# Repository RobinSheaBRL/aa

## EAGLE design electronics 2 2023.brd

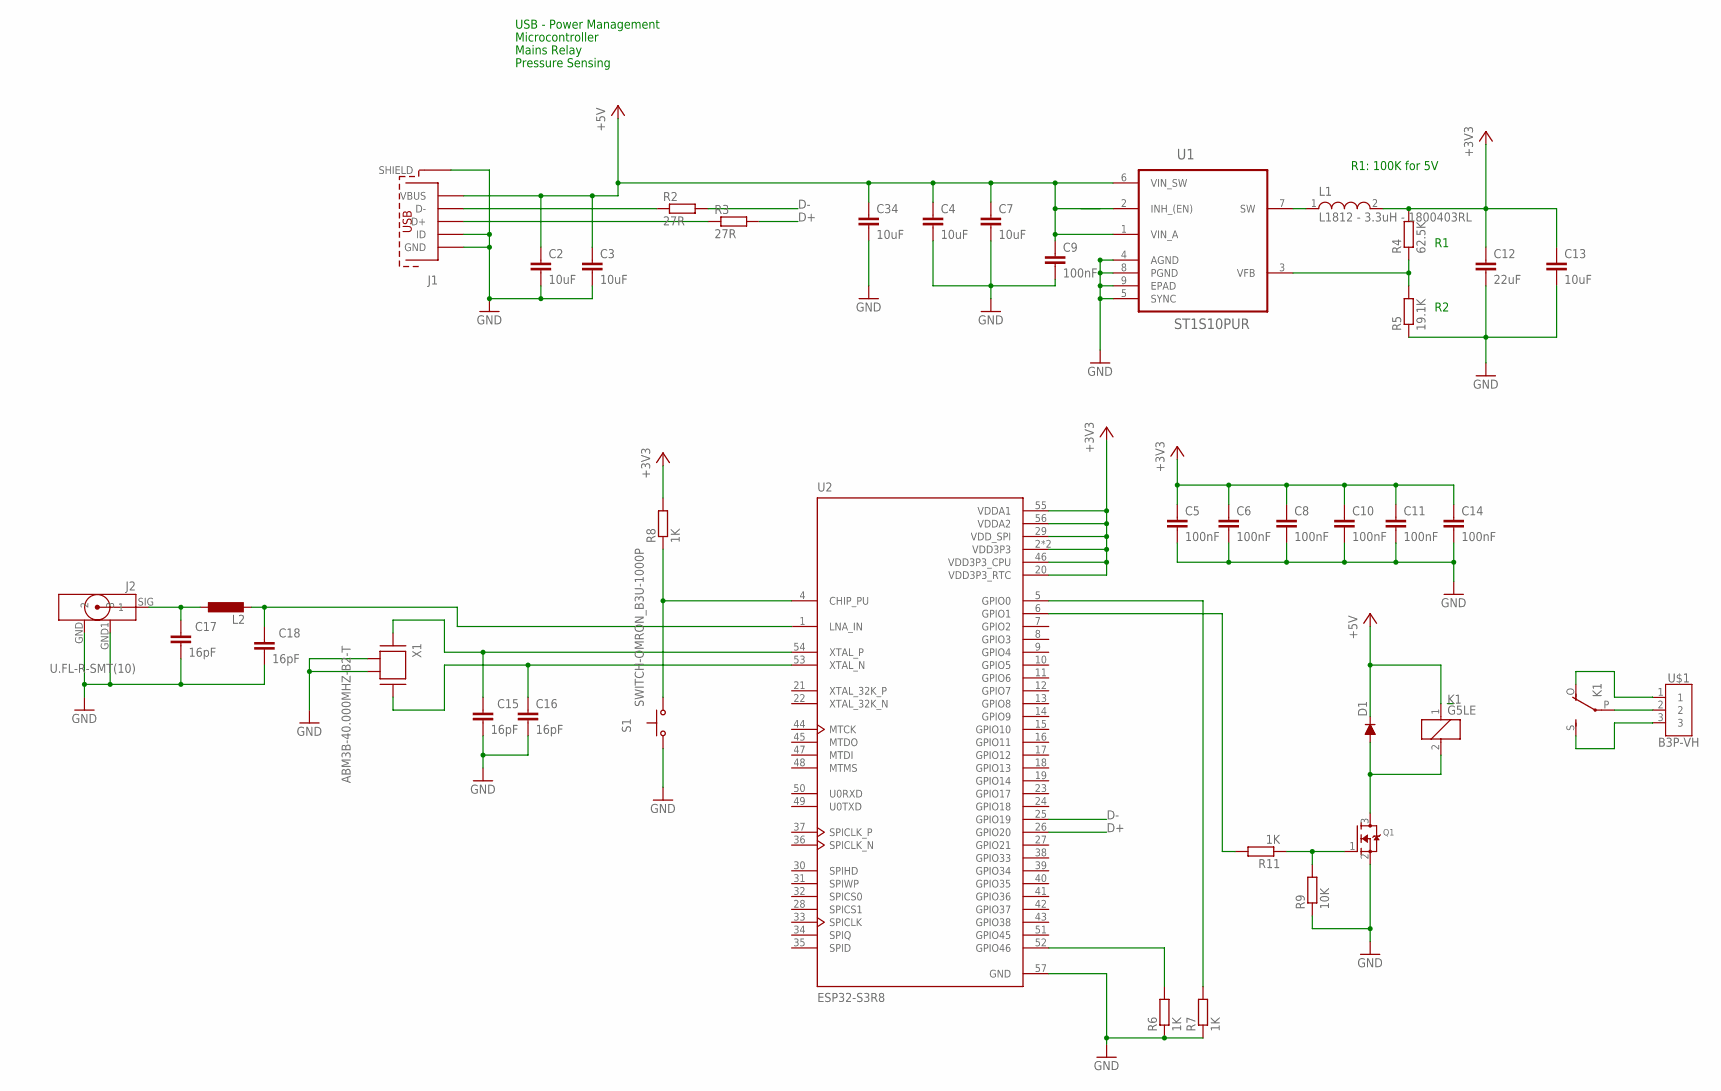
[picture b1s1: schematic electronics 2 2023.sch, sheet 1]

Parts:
C2, C3, C4, C7, C13, C34: 10uF; C0603
C5, C6, C8, C9, C10, C11, C14: 100nF; C0402
C12: 22uF; C0603
C15, C16, C17, C18: 16pF; C0402
D1: DIODE_DIODE-SOD123; DIODE_SOD123
J1: MICRO-USB-SOCKET; 629105136821
J2: U.FL-R-SMT(10)
K1: G5LE
L1: L1812 - 3.3uH - 1800403RL; L1812
L2: L-EUL2012C; L2012C
Q1: MOSFET-NREFLOW; SOT23
R2, R3: 27R; R0402
R4: 62.5K; R0402
R5: 19.1K; R0402
R6, R7, R8, R11: 1K; R0402
R9: 10K; R0402
S1: SWITCH-OMRON_B3U-1000P
U1: ST1S10PUR; DFN400X400X100-9N
U2: ESP32-S3R8; QFN40P700X700X90-57N
U$1: B3P-VH; B3P-VH_396_3N
X1: ABM3B-40.000MHZ-B2-T

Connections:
+3V3: C5.1, C6.1, C8.1, C10.1, C11.1, C12.1, C13.1, C14.1, L1.2, R4.2, R8.2, U2.2 (VDD3P3), U2.3 (VDD3P3), U2.20 (VDD3P3_RTC), U2.29 (VDD_SPI), U2.46 (VDD3P3_CPU), U2.55 (VDDA1), U2.56 (VDDA2); also elsewhere on the board
+5V: C2.1, C3.1, C4.1, C7.1, C9.1, C34.1, D1.C, J1.1 (VBUS), K1.1, U1.1 (VIN_A), U1.2 (INH_(EN)), U1.6 (VIN_SW)
D+: R3.2, U2.26 (GPIO20)
D-: R2.2, U2.25 (GPIO19)
GND: C2.2, C3.2, C4.2, C5.2, C6.2, C7.2, C8.2, C9.2, C10.2, C11.2, C12.2, C13.2, C14.2, C15.2, C16.2, C17.2, C18.2, C34.2, J1.4 (ID), J1.5 (GND), J1.SHELL (SHIELD), J1.SHELL1 (SHIELD), J1.SHELL2 (SHIELD), J1.SHELL3 (SHIELD), J2.GND (2), J2.GND1 (3), Q1.2 (S), R5.1, R6.1, R7.1, R9.1, S1.1, U1.4 (AGND), U1.5 (SYNC), U1.8 (PGND), U1.9 (EPAD), U2.57 (GND), X1.2, X1.4; also elsewhere on the board
unnamed: J1.2 (D-), R2.1
unnamed: J1.3 (D+), R3.1
unnamed: R4.1, R5.2, U1.3 (VFB)
unnamed: L1.1, U1.7 (SW)
unnamed: C15.1, U2.54 (XTAL_P), X1.1
unnamed: C16.1, U2.53 (XTAL_N), X1.3
unnamed: R6.2, U2.52 (GPIO46)
unnamed: R7.2, U2.5 (GPIO0)
unnamed: C18.1, L2.2, U2.1 (LNA_IN)
unnamed: C17.1, J2.SIG (1), L2.1
unnamed: R8.1, S1.2 (S), U2.4 (CHIP_PU)
unnamed: D1.A, K1.2, Q1.3 (D)
unnamed: K1.P, U$1.2
unnamed: Q1.1 (G), R9.2, R11.1
unnamed: K1.O, U$1.1
unnamed: R11.2, U2.6 (GPIO1)
unnamed: K1.S, U$1.3

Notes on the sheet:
USB - Power Management
Microcontroller
Mains Relay
Pressure Sensing
R1: 100K for 5V

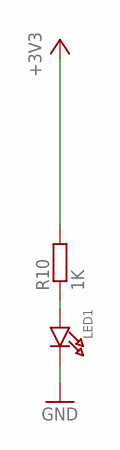
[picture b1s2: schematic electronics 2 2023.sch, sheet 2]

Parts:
LED1: LED0603; CHIPLED_0603
R10: 1K; R0402

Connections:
+3V3: R10.2; also elsewhere on the board
GND: LED1.C; also elsewhere on the board
unnamed: LED1.A, R10.1

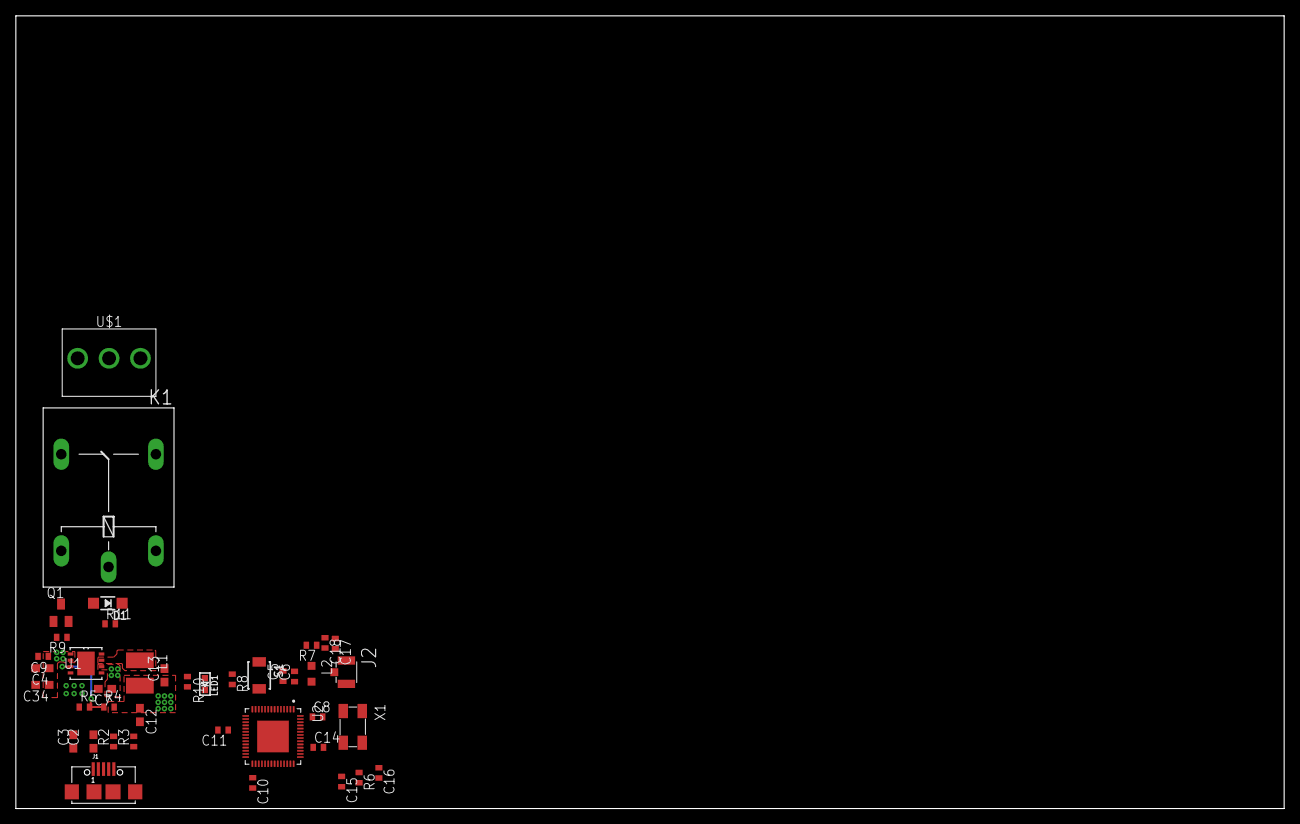
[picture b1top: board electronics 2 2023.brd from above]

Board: 2 copper layers, 160.0 x 100.0 mm, 41 parts (0 on the bottom side), 23 nets.

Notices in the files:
parts and their libraries:
2mm connector: This work is placed in the public domain, and may be freely used for commercial and non-commercial work with the following conditions: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
